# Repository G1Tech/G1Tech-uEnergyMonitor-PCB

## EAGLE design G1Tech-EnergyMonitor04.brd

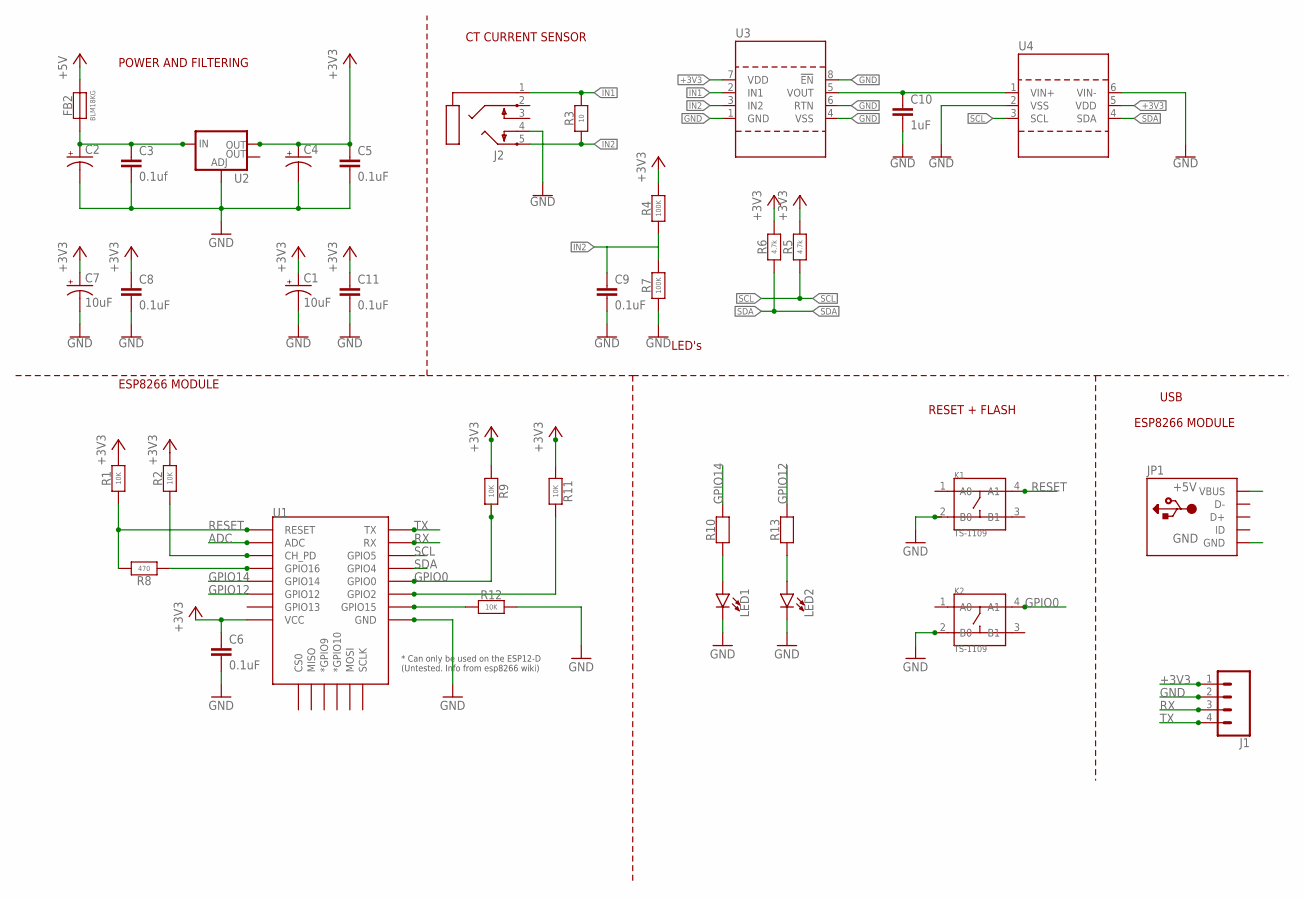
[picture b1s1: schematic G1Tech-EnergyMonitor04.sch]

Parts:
C1, C7: 10uF; TYPE-A
C2, C4: C-TYPE-A; TYPE-A
C3: 0.1uf; C0805
C5: 0.1uF; C0805
C6, C8, C9, C11: 0.1uF; C0603
C10: 1uF; C0603
FB2: BLM18KG; FB-0603
J1: CONN_04; 1X04
J2: PJ-3126-5A
JP1: USB-MICRO-B-1A; USB-MICRO
K1, K2: TS-1109; SW4-6.0X6.0X5.0MM
LED1, LED2: LED0603
R1, R2, R9, R11, R12: 10K; YAGEO-R0603
R3: 10; YAGEO-R0603
R4, R7: 100K; YAGEO-R0603
R5, R6: 4.7k; YAGEO-R0603
R8: 470; YAGEO-R0603
R10, R13: YAGEO-R0603
U1: ESP12ESMD; ESP12E-SMD
U2: V_REG_LM1117SOT223; SOT223
U3: LTC1966; MS8
U4: MCP3425; SOT23-6

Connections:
+3V3: C1.A, C4.A, C5.1, C6.1, C7.A, C8.1, C11.1, J1.1, R1.2, R2.2, R4.2, R5.2, R6.2, R9.1, R11.1, U1.VCC, U2.2 (OUT), U3.7 (VDD), U4.5 (VDD)
+5V: FB2.2, JP1.VBUS
ADC: U1.ADC
GND: C1.C, C2.C, C3.2, C4.C, C5.2, C6.2, C7.C, C8.2, C9.2, C10.2, C11.2, J1.2, J2.4, JP1.GND, K1.2 (B0), K2.2 (B0), LED1.C, LED2.C, R7.1, R12.2, U1.GND, U2.1 (ADJ), U3.1 (GND), U3.4 (VSS), U3.6 (RTN), U3.8 (!EN), U4.2 (VSS), U4.6 (VIN-)
GPIO0: K2.4 (A1), R9.2, U1.GPIO0
GPIO12: R13.2, U1.GPIO12
GPIO14: R10.2, U1.GPIO14
IN1: J2.1, R3.2, U3.2 (IN1)
IN2: C9.1, J2.5, R3.1, R4.1, R7.2, U3.3 (IN2)
unnamed: R12.1, U1.GPIO15
unnamed: R11.2, U1.GPIO2
unnamed: LED1.A, R10.1
unnamed: C2.A, C3.1, FB2.1, U2.3 (IN)
unnamed: R8.1, U1.GPIO16
unnamed: LED2.A, R13.1
unnamed: R2.1, U1.CH_PD
RESET: K1.4 (A1), R1.1, R8.2, U1.RESET
RX: J1.3, U1.RXD0 (RX)
SCL: R5.1, U1.GPIO5, U4.3 (SCL)
SDA: R6.1, U1.GPIO4, U4.4 (SDA)
TX: J1.4, U1.TXD0 (TX)
VIN+: C10.1, U3.5 (VOUT), U4.1 (VIN+)

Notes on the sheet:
POWER AND FILTERING
ESP8266 MODULE
LED's
RESET + FLASH
USB
CT CURRENT SENSOR

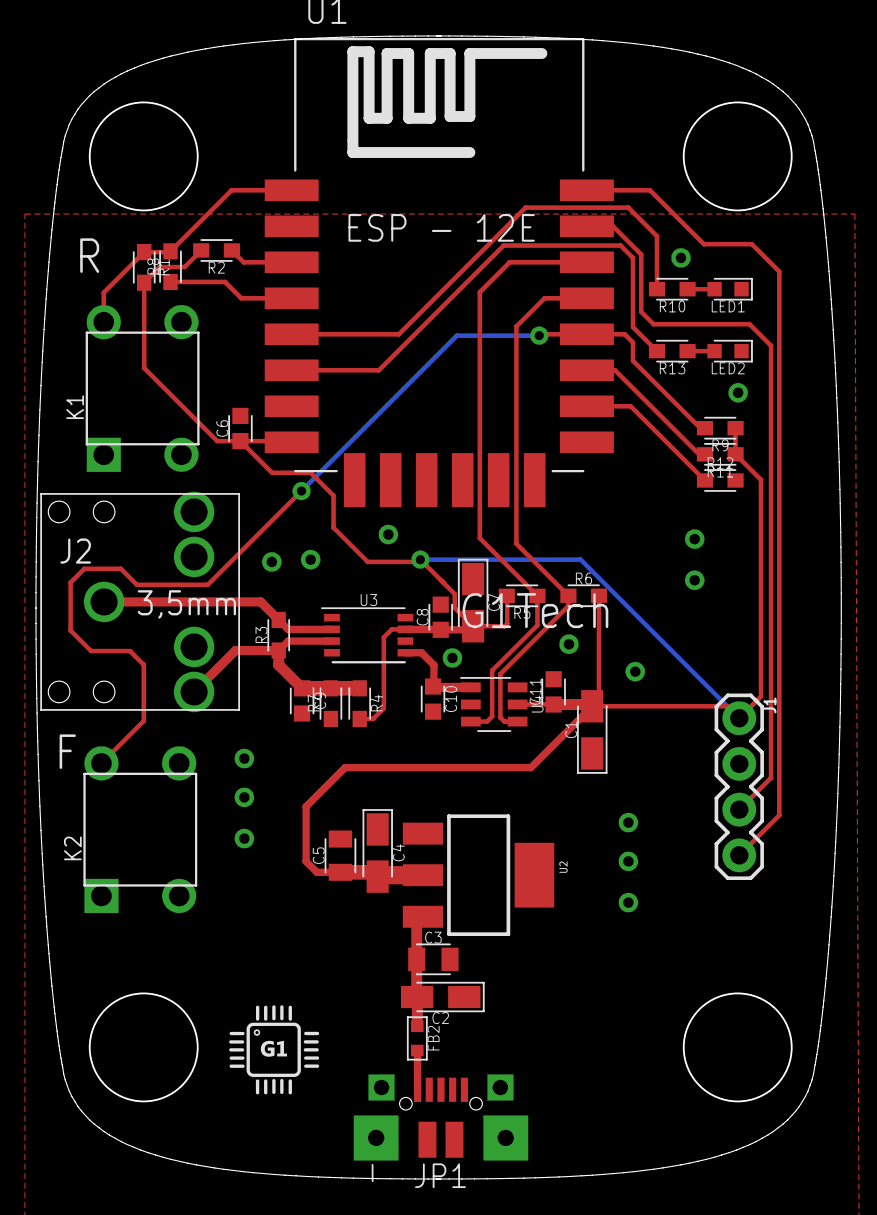
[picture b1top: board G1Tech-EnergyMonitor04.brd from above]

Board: 2 copper layers, 44.6 x 63.4 mm, 38 parts (1 on the bottom side), 21 nets.

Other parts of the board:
U$1: LOGO-G1TECH-5MM
U$3: LOGO-G1TECH-10MM

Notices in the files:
parts and their libraries:
SparkFun-Connectors: Licensing: Creative Commons ShareAlike 4.0 International - https://creativecommons.org/licenses/by-sa/4.0
